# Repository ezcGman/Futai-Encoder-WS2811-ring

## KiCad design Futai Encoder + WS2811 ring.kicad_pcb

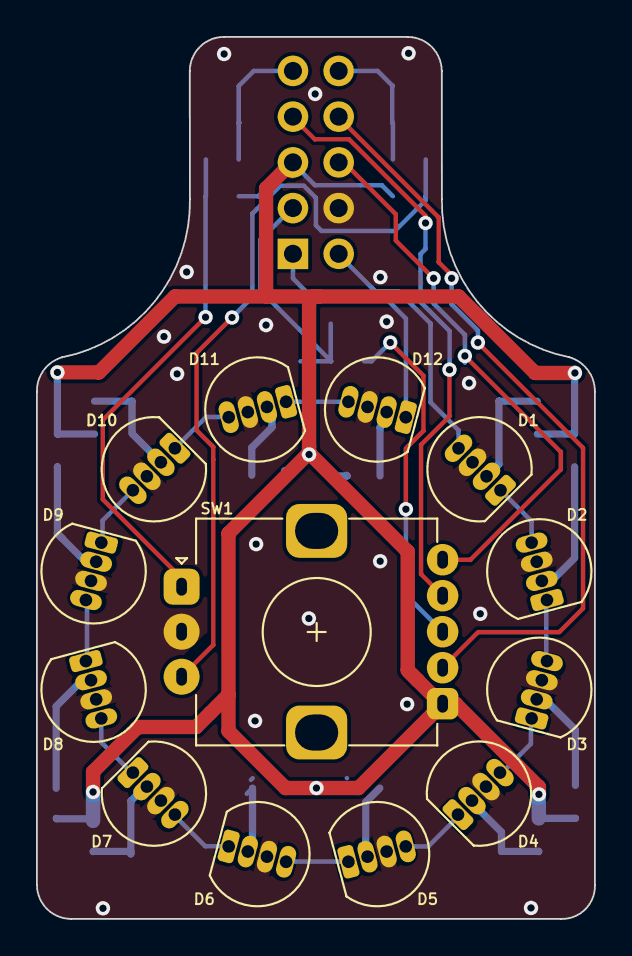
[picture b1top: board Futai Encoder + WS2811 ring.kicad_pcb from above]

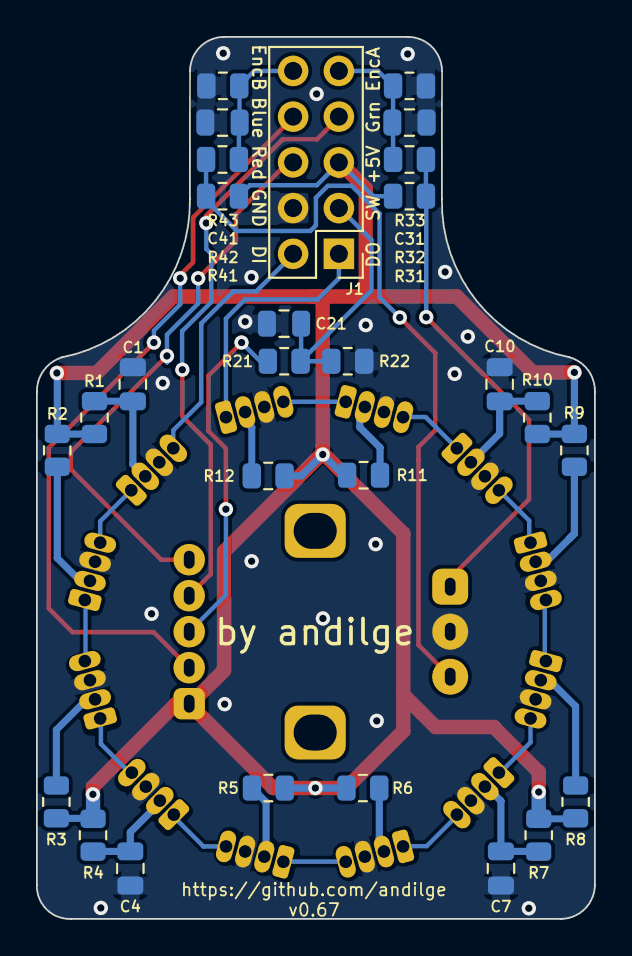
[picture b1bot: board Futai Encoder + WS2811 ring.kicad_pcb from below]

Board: 2 copper layers, 31.0 x 49.0 mm, 41 parts (28 on the bottom side), 36 nets.

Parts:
C1, C4, C7, C10, C21: 100n; C_0805_2012Metric
C31, C41: 10n; C_0805_2012Metric
D1, D2, D3, D4, D5, D6, D7, D8, D9, D10, D11, D12: WS2812D; WS2811-THT-LED
J1: Conn_02x05_Top_Bottom; PinHeader_2x05_P2.54mm_Vertical
R1, R2, R3, R4, R5, R6, R7, R8, R9, R10, R11, R12: 130; R_0805_2012Metric
R21: 33k; R_0805_2012Metric
R22: 68k; R_0805_2012Metric
R31, R32, R41, R42: 10k; R_0805_2012Metric
R33, R43: 39k; R_0805_2012Metric
SW1: RotaryEncoder_Switch_RGB; LED_RotaryEncoder_EC12_Switch_Vertical_H20mm

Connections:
+5V: J1.5, R1.1, R2.1, R3.1, R4.1, R5.1, R6.1, R7.1, R8.1, R9.1, R10.1, R11.1, R12.1, R31.1, R41.1, SW1.1 (C+)
BLU: J1.8, SW1.2 (BLU)
DIN: D1.4 (DIN), J1.2
DOUT: D12.1 (DOUT), J1.1
ENC_A: R31.2, R32.2, SW1.A
ENC_B: R41.2, R42.2, SW1.B
GND: C1.2, C4.1, C7.2, C10.2, C21.2, C31.1, C41.1, D1.3 (VSS), D2.3 (VSS), D3.3 (VSS), D4.3 (VSS), D5.3 (VSS), D6.3 (VSS), D7.3 (VSS), D8.3 (VSS), D9.3 (VSS), D10.3 (VSS), D11.3 (VSS), D12.3 (VSS), J1.4, R22.1, R33.1, R43.1, SW1.C (C-)
GRE: J1.7, SW1.4 (GRE)
unnamed: C1.1, D1.2 (VDD), R1.2
unnamed: C4.2, D4.2 (VDD), R4.2
unnamed: C7.1, D7.2 (VDD), R7.2
unnamed: C10.1, D10.2 (VDD), R10.2
unnamed: C21.1, J1.3, R21.1, R22.2
unnamed: C31.2, J1.9, R32.1, R33.2
unnamed: C41.2, J1.10, R42.1, R43.2
unnamed: D1.1 (DOUT), D2.4 (DIN)
unnamed: D2.1 (DOUT), D3.4 (DIN)
unnamed: D2.2 (VDD), R2.2
unnamed: D3.1 (DOUT), D4.4 (DIN)
unnamed: D3.2 (VDD), R3.2
unnamed: D4.1 (DOUT), D5.4 (DIN)
unnamed: D5.1 (DOUT), D6.4 (DIN)
unnamed: D5.2 (VDD), R5.2
unnamed: D6.1 (DOUT), D7.4 (DIN)
unnamed: D6.2 (VDD), R6.2
unnamed: D7.1 (DOUT), D8.4 (DIN)
unnamed: D8.1 (DOUT), D9.4 (DIN)
unnamed: D8.2 (VDD), R8.2
unnamed: D9.2 (VDD), R9.2
unnamed: D10.1 (DOUT), D11.4 (DIN)
unnamed: D9.1 (DOUT), D10.4 (DIN)
unnamed: D11.1 (DOUT), D12.4 (DIN)
unnamed: D11.2 (VDD), R11.2
unnamed: D12.2 (VDD), R12.2
RED: J1.6, SW1.5 (RED)
SWC: R21.2, SW1.3 (SWC)

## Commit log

2022-01-18 v067: Resized silkscreens to 0.6, 100% aligned things to each other to satisfy my inner monk
